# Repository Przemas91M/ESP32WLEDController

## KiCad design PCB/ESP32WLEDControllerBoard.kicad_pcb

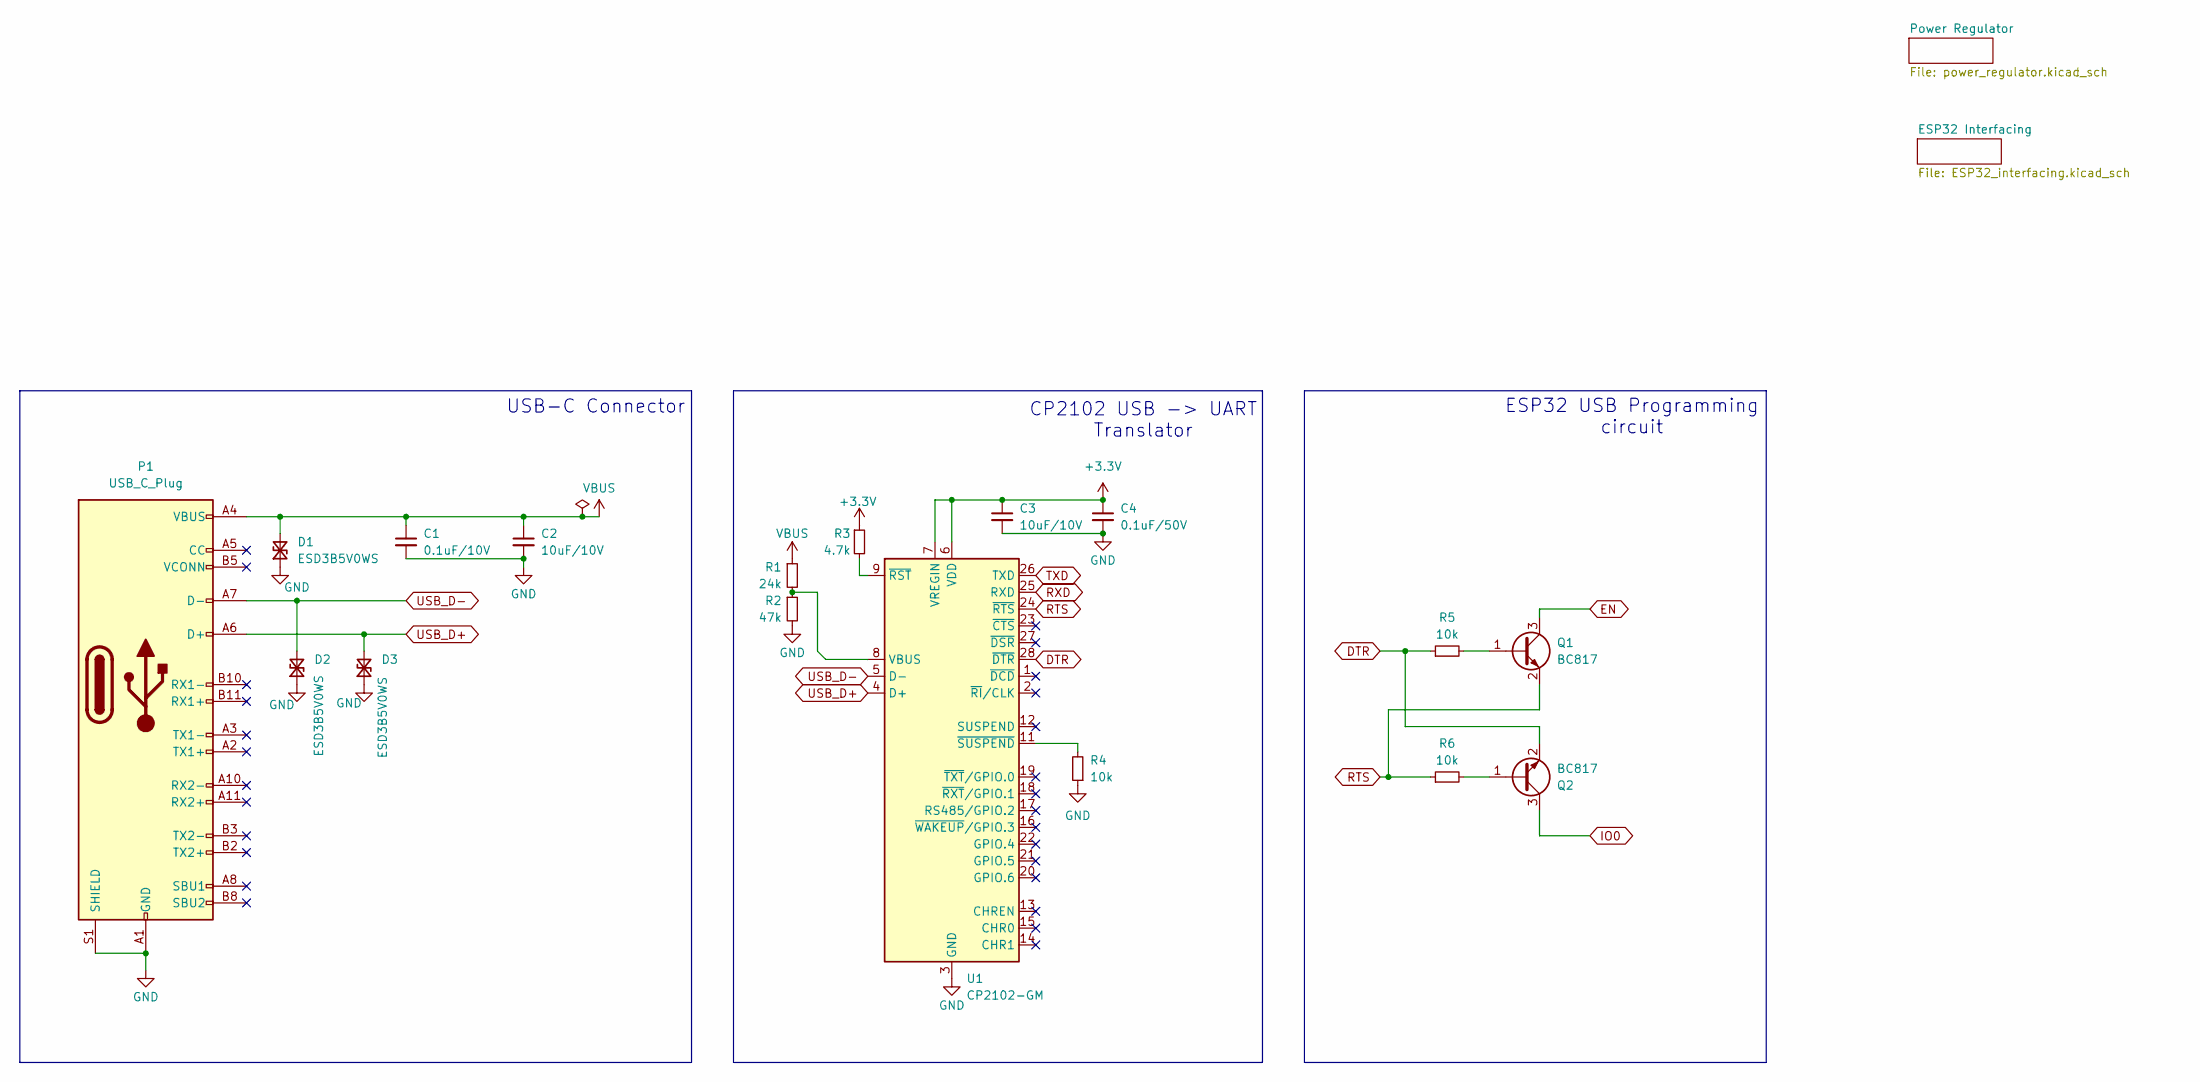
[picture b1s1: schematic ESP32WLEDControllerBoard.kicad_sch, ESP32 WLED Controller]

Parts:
C1: 0.1uF/10V; C_0805_2012Metric_Pad1.18x1.45mm_HandSolder
C2, C3: 10uF/10V; C_1206_3216Metric_Pad1.33x1.80mm_HandSolder
C4: 0.1uF/50V; C_0805_2012Metric_Pad1.18x1.45mm_HandSolder
D1, D2, D3: ESD3B5V0WS; D_SOD-323_HandSoldering
P1: USB_C_Plug; USB_C_Receptacle_GCT_USB4110
Q1, Q2: BC817; SOT-23
R1: 24k; R_0603_1608Metric_Pad0.98x0.95mm_HandSolder
R2: 47k; R_0603_1608Metric_Pad0.98x0.95mm_HandSolder
R3: 4.7k; R_0603_1608Metric_Pad0.98x0.95mm_HandSolder
R4, R5, R6: 10k; R_0603_1608Metric_Pad0.98x0.95mm_HandSolder
U1: CP2102-GM; QFN-28-1EP_5x5mm_P0.5mm_EP3.35x3.35mm

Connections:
+3.3V: C3.1, C4.1, R3.1, U1.6 (VDD), U1.7 (VREGIN); also elsewhere on the board
DTR: Q2.2 (E), R5.1, U1.28 (~DTR)
EN: Q1.3 (C); also elsewhere on the board
GND: C1.2, C2.2, C3.2, C4.2, D1.1 (A1), D2.1 (A1), D3.1 (A1), P1.A1 (GND), P1.A12 (GND), P1.B1 (GND), P1.B12 (GND), P1.S1 (SHIELD), R2.2, R4.1, U1.3 (GND), U1.29 (GND); also elsewhere on the board
IO0: Q2.3 (C); also elsewhere on the board
unnamed: Q1.1 (B), R5.2
unnamed: Q2.1 (B), R6.2
unnamed: R1.2, R2.1, U1.8 (VBUS)
unnamed: R3.2, U1.9 (~RST)
unnamed: R4.2, U1.11 (~SUSPEND)
RTS: Q1.2 (E), R6.1, U1.24 (~RTS)
RXD: U1.25 (RXD); also elsewhere on the board
TXD: U1.26 (TXD); also elsewhere on the board
USB_D+: D3.2 (A2), P1.A6 (D+), U1.4 (D+)
USB_D-: D2.2 (A2), P1.A7 (D-), U1.5 (D-)
VBUS: C1.1, C2.1, D1.2 (A2), P1.A4 (VBUS), P1.A9 (VBUS), P1.B4 (VBUS), P1.B9 (VBUS), R1.1; also elsewhere on the board

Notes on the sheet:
USB-C Connector
CP2102 USB -> UART Translator
ESP32 USB Programming circuit

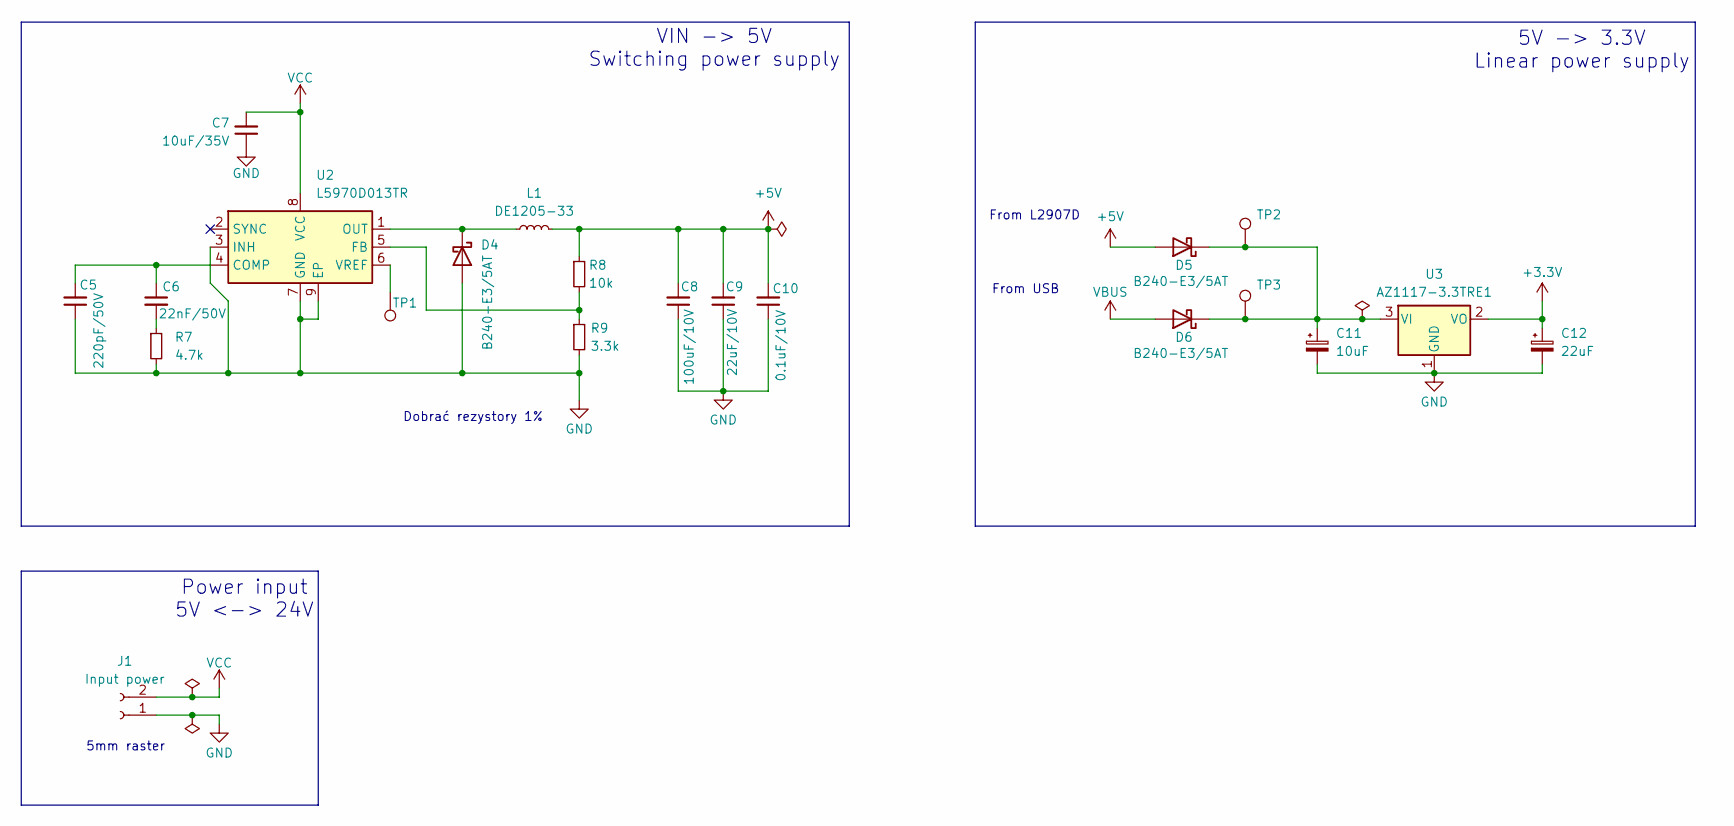
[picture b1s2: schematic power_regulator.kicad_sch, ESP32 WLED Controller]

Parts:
C5: 220pF/50V; C_0805_2012Metric_Pad1.18x1.45mm_HandSolder
C6: 22nF/50V; C_0805_2012Metric_Pad1.18x1.45mm_HandSolder
C7: 10uF/35V; C_1206_3216Metric_Pad1.33x1.80mm_HandSolder
C8: 100uF/10V; C_1210_3225Metric_Pad1.33x2.70mm_HandSolder
C9: 22uF/10V; C_0805_2012Metric_Pad1.18x1.45mm_HandSolder
C10: 0.1uF/10V; C_0805_2012Metric_Pad1.18x1.45mm_HandSolder
C11: 10uF; C_1206_3216Metric_Pad1.33x1.80mm_HandSolder
C12: 22uF; C_0805_2012Metric_Pad1.18x1.45mm_HandSolder
D4: B240-E3/5AT; D_SMA-SMB_Universal_Handsoldering
D5, D6: B240-E3/5AT; D_SMA_Handsoldering
J1: Input power; JST_NV_B02P-NV_1x02_P5.00mm_Vertical
L1: DE1205-33; L_Sunlord_SWRB1205S
R7: 4.7k; R_0603_1608Metric_Pad0.98x0.95mm_HandSolder
R8: 10k; R_0603_1608Metric_Pad0.98x0.95mm_HandSolder
R9: 3.3k; R_0603_1608Metric_Pad0.98x0.95mm_HandSolder
TP1: TestPoint; TestPoint_Pad_D2.0mm
TP2: 5V Test; TestPoint_Pad_D2.0mm
TP3: VBUS Test; TestPoint_Pad_D2.0mm
U2: L5970D013TR; HSOP-8-1EP_3.9x4.9mm_P1.27mm_EP2.41x3.1mm_ThermalVias
U3: AZ1117-3.3TRE1; SOT-223-3_TabPin2

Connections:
+3.3V: C12.1, U3.2 (VO); also elsewhere on the board
GND: C5.1, C7.1, C8.1, C9.1, C10.1, C11.2, C12.2, D4.2 (A), J1.1, R7.2, R9.2, U2.3 (INH), U2.7 (GND), U2.9 (EP), U3.1 (GND); also elsewhere on the board
unnamed: C6.2, R7.1
unnamed: D4.1 (K), L1.1, U2.1 (OUT)
unnamed: C11.1, D5.1 (K), D6.1 (K), TP2.1, TP3.1, U3.3 (VI)
unnamed: C5.2, C6.1, U2.4 (COMP)
unnamed: R8.2, R9.1, U2.5 (FB)
unnamed: TP1.1, U2.6 (VREF)
STRIP1_DIN: C8.2, C9.2, C10.2, D5.2 (A), L1.2, R8.1; also elsewhere on the board
VBUS: D6.2 (A); also elsewhere on the board
VCC: C7.2, J1.2, U2.8 (VCC); also elsewhere on the board

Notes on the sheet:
From USB
Dobrać rezystory 1%
5V -> 3.3V Linear power supply
From L2907D
5mm raster
VIN -> 5V Switching power supply
Power input 5V <-> 24V

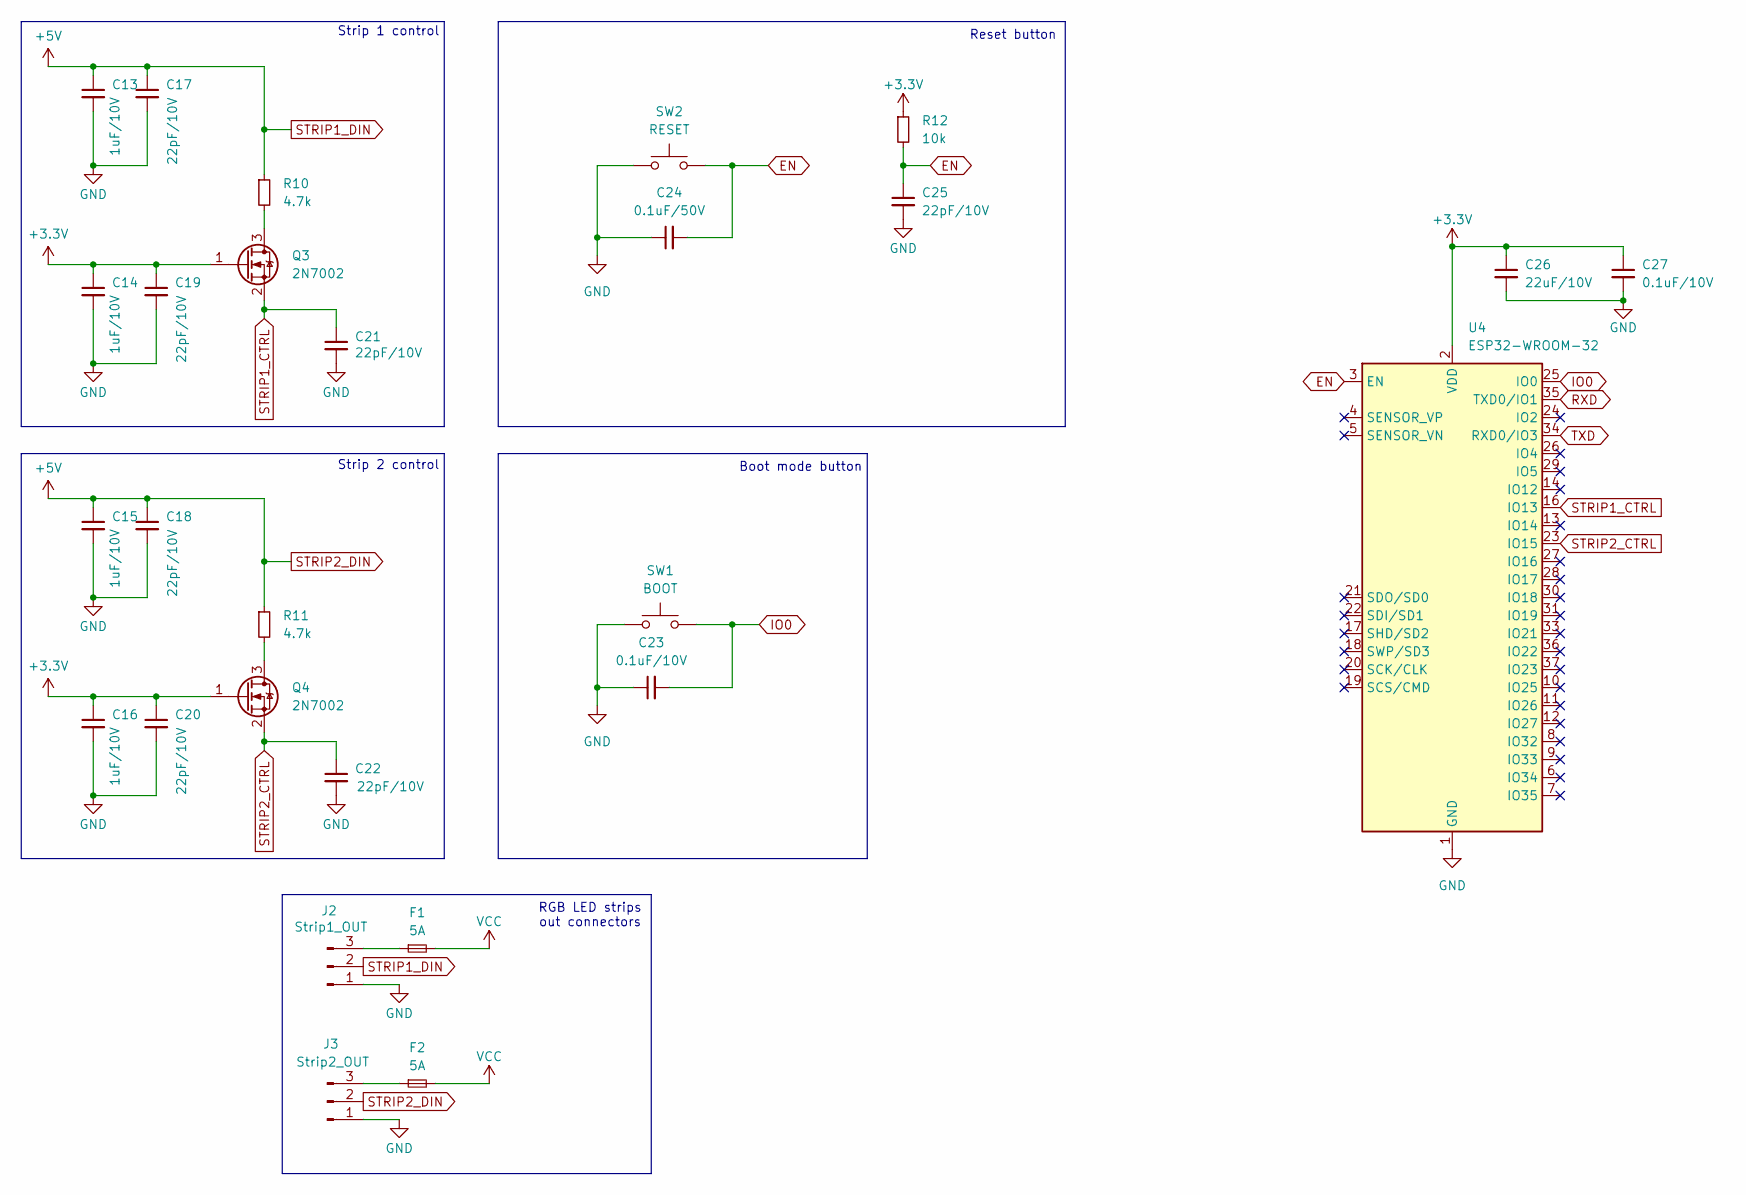
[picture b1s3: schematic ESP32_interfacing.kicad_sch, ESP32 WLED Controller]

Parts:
C13, C14, C15, C16: 1uF/10V; C_0805_2012Metric_Pad1.18x1.45mm_HandSolder
C17, C18, C19, C20, C21, C22, C25: 22pF/10V; C_0805_2012Metric_Pad1.18x1.45mm_HandSolder
C23, C27: 0.1uF/10V; C_0805_2012Metric_Pad1.18x1.45mm_HandSolder
C24: 0.1uF/50V; C_0805_2012Metric_Pad1.18x1.45mm_HandSolder
C26: 22uF/10V; C_0805_2012Metric_Pad1.18x1.45mm_HandSolder
F1, F2: 5A; Fuse_2410_BelFuse
J2: Strip1_OUT; PhoenixContact_MCV_1,5_3-G-3.81_1x03_P3.81mm_Vertical
J3: Strip2_OUT; PhoenixContact_MCV_1,5_3-G-3.81_1x03_P3.81mm_Vertical
Q3, Q4: 2N7002; SOT-23
R10, R11: 4.7k; R_0603_1608Metric_Pad0.98x0.95mm_HandSolder
R12: 10k; R_0603_1608Metric_Pad0.98x0.95mm_HandSolder
SW1: BOOT; SW_SPST_CK_RS282G05A3
SW2: RESET; SW_SPST_CK_RS282G05A3
U4: ESP32-WROOM-32

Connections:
+3.3V: C14.1, C16.1, C19.1, C20.1, C26.1, C27.1, Q3.1 (G), Q4.1 (G), R12.1, U4.2 (VDD); also elsewhere on the board
EN: C24.2, C25.1, R12.2, SW2.2, U4.3 (EN); also elsewhere on the board
GND: C13.2, C14.2, C15.2, C16.2, C17.2, C18.2, C19.2, C20.2, C21.2, C22.2, C23.1, C24.1, C25.2, C26.2, C27.2, J2.1, J3.1, SW1.1, SW2.1, U4.1 (GND), U4.15 (GND), U4.38 (GND), U4.39 (GND); also elsewhere on the board
IO0: C23.2, SW1.2, U4.25 (IO0); also elsewhere on the board
unnamed: F1.1, J2.3
unnamed: F2.1, J3.3
unnamed: Q3.3 (D), R10.2
unnamed: Q4.3 (D), R11.2
RXD: U4.35 (TXD0/IO1); also elsewhere on the board
STRIP1_CTRL: C21.1, Q3.2 (S), U4.16 (IO13)
STRIP1_DIN: C13.1, C15.1, C17.1, C18.1, J2.2, J3.2, R10.1, R11.1; also elsewhere on the board
STRIP2_CTRL: C22.1, Q4.2 (S), U4.23 (IO15)
TXD: U4.34 (RXD0/IO3); also elsewhere on the board
VCC: F1.2, F2.2; also elsewhere on the board

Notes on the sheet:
Strip 2 control
Strip 1 control
RGB LED strips out connectors
Reset button
Boot mode button

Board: 2 copper layers, 65 parts (0 on the bottom side), 30 nets, no tracks yet.

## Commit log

2025-04-14 Board with USB-C connector and programming chip
